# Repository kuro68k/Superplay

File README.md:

# SUPERPLAY

SUPERPLAY is an arcade joystick controller system. It consists of serveral parts.

The main SUPERPLAY PCB is fitted to the joystick and can either connect via USB or a custom KBUS. Both use the same USB cable. Configuration is via a Windows app called SPConfig.

SUPERPLAY supports up to 16 buttons, multiple autofire configurations with selectable fire rate, multiple options for switching modes and rotary joysticks (Seimitsu LS-30, used by SNK) for games like Midnight Resistance. Rotary joystick support is compatible with MAME, and configurable. SUPERPLAY also supports expansion boards via an expansion header, similar to Arduino sheilds.

####True zero lag

Many joystick controllers claim to be zero lag, but as FPS players know USB introduces some delay. USB HID devices are polled at 120Hz maximum, resulting in up to 8ms of lag (1/2 a frame at 60Hz). FPS players hack the Windows mouse driver to increase the poll rate, but it doesn't work for joysticks.

SUPERPLAY uses the excellent vJoy (vjoystick.sourceforge.net) and a custom USB interface to increase the polling rate to 1000Hz, reducing lag down to 1ms maximum. This gives true zero, arcade/console levels of input lag (i.e. none).

####Autofire

SUPERPLAY has a special autofire implementation that allows the player to set a precise frequency, and ensures that a button press is always registered when the button is first pushed. Simple autofire systems switch in a square wave, so the button press is sometimes not registered until the "on" part of the square wave comes around.

####KBUS

Aside from USB, SUPERPLAY can be connected to KBUS devices. Currently under development are a supergun with KBUS support, and a number of "recievers". Recievers connect to games consoles. The first is planned to support Playstation 1/2, Saturn and Dreamcast. Unfortunately due to licencing agreements Dreamcast support will not be published.

KBUS uses a simple 3.3V "RS232" compatible protocol, that can be easily implemented on low cost microcontrollers.

####Other stuff

A HID based USB bootloader will be provided for firmware and configuration updates. See my other projects for code.

The main SUPERPLAY PCB uses an XMEGA 128A3U microcontroller. This might be revised down to a 64KB in future. The project opens with Atmel Studio 6.2. Schematic and gerbers created in Eagle. V1.0 hardware has been built, V1.1 corrects a few issues.

SPConfig is built in Visual Studio 2013 Community Edition. I uses MahApps.Metro to create a "modern" UI.

Everything is licenced under GPL v3.

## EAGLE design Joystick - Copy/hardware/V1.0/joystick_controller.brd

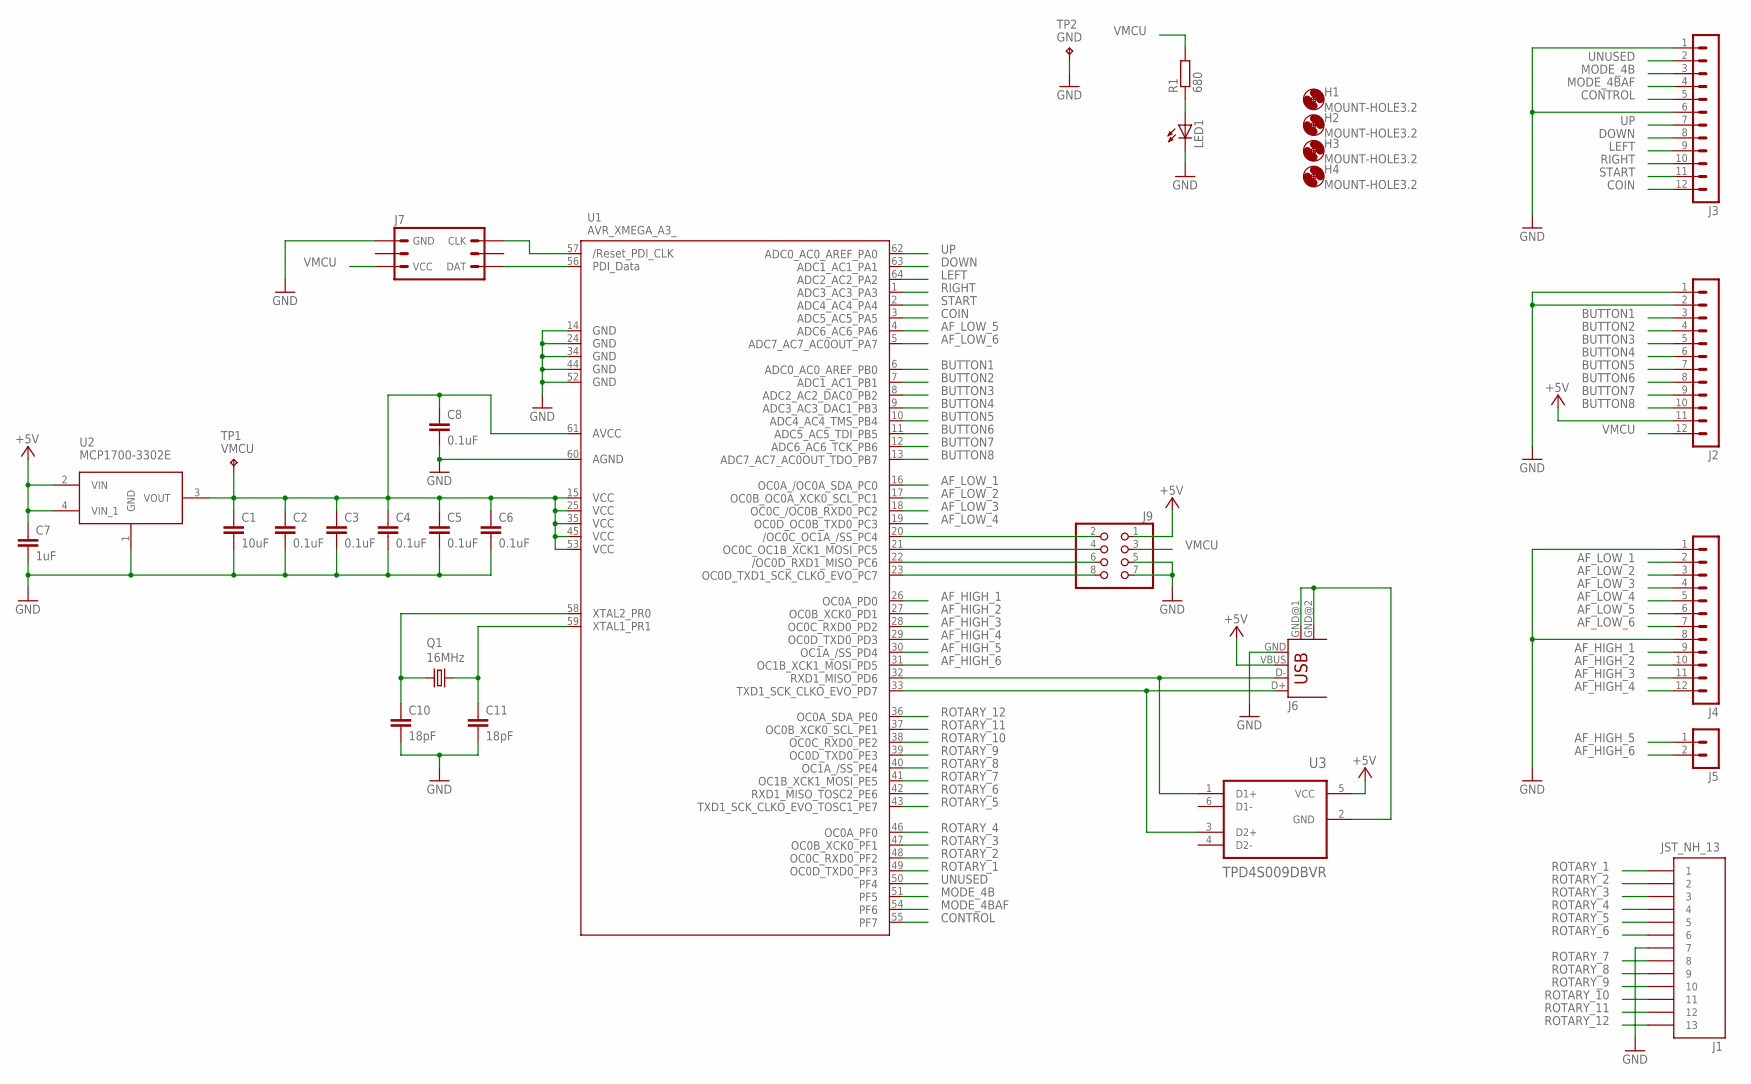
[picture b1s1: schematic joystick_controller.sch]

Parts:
C1: 10uF; C0805
C2, C3, C4, C5, C6, C8: 0.1uF; C0805
C7: 1uF; C0805
C10, C11: 18pF; C0805
H1, H2, H3, H4: MOUNT-HOLE3.2; 3,2
J1: JST_NH_13; JST_NH_13_RA
J2, J3, J4: CON-3.5TERM-12
J5: CON-3.5TERM-2
J6: USB-B-H
J7: PDI_HEADER; MA03-2
J9: PINHD-2X4; 2X04
LED1: LEDCHIP-LED0805; CHIP-LED0805
Q1: 16MHz; HC49/S
R1: 680; R0805
TP1: VMCU; HARWIN-S1751-46
TP2: GND; HARWIN-S1751-46
U1: AVR_XMEGA_A3_; TQFP64
U2: MCP1700-3302E; SOT150P400X160-4N
U3: TPD4S009DBVR; SOT95P280X145-6N

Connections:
+5V: C7.1, J2.11, J6.VBUS, J9.1, U2.2 (VIN), U2.4 (VIN_1), U3.5 (VCC)
AF_HIGH_1: J4.9, U1.26 (PD0)
AF_HIGH_2: J4.10, U1.27 (PD1)
AF_HIGH_3: J4.11, U1.28 (PD2)
AF_HIGH_4: J4.12, U1.29 (PD3)
AF_HIGH_5: J5.1, U1.30 (PD4)
AF_HIGH_6: J5.2, U1.31 (PD5)
AF_LOW_1: J4.2, U1.16 (PC0)
AF_LOW_2: J4.3, U1.17 (PC1)
AF_LOW_3: J4.4, U1.18 (PC2)
AF_LOW_4: J4.5, U1.19 (PC3)
AF_LOW_5: J4.6, U1.4 (PA6)
AF_LOW_6: J4.7, U1.5 (PA7)
BUTTON1: J2.3, U1.6 (PB0)
BUTTON2: J2.4, U1.7 (PB1)
BUTTON3: J2.5, U1.8 (PB2)
BUTTON4: J2.6, U1.9 (PB3)
BUTTON5: J2.7, U1.10 (PB4)
BUTTON6: J2.8, U1.11 (PB5)
BUTTON7: J2.9, U1.12 (PB6)
BUTTON8: J2.10, U1.13 (PB7)
COIN: J3.12, U1.3 (PA5)
CONTROL: J3.5, U1.55 (PF7)
DOWN: J3.8, U1.63 (PA1)
D_M: J6.D-, U1.32 (PD6), U3.1 (D1+)
D_P: J6.D+, U1.33 (PD7), U3.3 (D2+)
GND: C1.2, C2.2, C3.2, C4.2, C5.2, C6.2, C7.2, C8.2, C10.2, C11.2, J1.7, J2.1, J2.2, J3.1, J3.6, J4.1, J4.8, J6.GND, J7.6 (GND), J9.5, J9.7, LED1.C, TP2.P$1, U1.14 (GND1), U1.24 (GND2), U1.34 (GND3), U1.44 (GND4), U1.52 (GND5), U1.60 (AGND), U2.1 (GND)
LEFT: J3.9, U1.64 (PA2)
MODE_4B: J3.3, U1.51 (PF5)
MODE_4BAF: J3.4, U1.54 (PF6)
unnamed: LED1.A, R1.1
unnamed: J7.1 (DAT), U1.56 (PDI_DATA)
unnamed: J7.5 (CLK), U1.57 (RESET)
unnamed: J6.GND@1 (GND), J6.GND@2 (GND), U3.2 (GND)
unnamed: J9.8, U1.23 (PC7)
unnamed: J9.6, U1.22 (PC6)
unnamed: J9.4, U1.21 (PC5)
unnamed: J9.2, U1.20 (PC4)
unnamed: C11.1, Q1.2, U1.59 (PR1)
unnamed: C10.1, Q1.1, U1.58 (PR0)
RIGHT: J3.10, U1.1 (PA3)
ROTARY_1: J1.1, U1.49 (PF3)
ROTARY_2: J1.2, U1.48 (PF2)
ROTARY_3: J1.3, U1.47 (PF1)
ROTARY_4: J1.4, U1.46 (PF0)
ROTARY_5: J1.5, U1.43 (PE7)
ROTARY_6: J1.6, U1.42 (PE6)
ROTARY_7: J1.8, U1.41 (PE5)
ROTARY_8: J1.9, U1.40 (PE4)
ROTARY_9: J1.10, U1.39 (PE3)
ROTARY_10: J1.11, U1.38 (PE2)
ROTARY_11: J1.12, U1.37 (PE1)
ROTARY_12: J1.13, U1.36 (PE0)
START: J3.11, U1.2 (PA4)
UNUSED: J3.2, U1.50 (PF4)
UP: J3.7, U1.62 (PA0)
VMCU: C1.1, C2.1, C3.1, C4.1, C5.1, C6.1, C8.1, J2.12, J7.2 (VCC), J9.3, R1.2, TP1.P$1, U1.15 (VCC1), U1.25 (VCC2), U1.35 (VCC3), U1.45 (VCC4), U1.53 (VCC5), U1.61 (AVCC), U2.3 (VOUT)

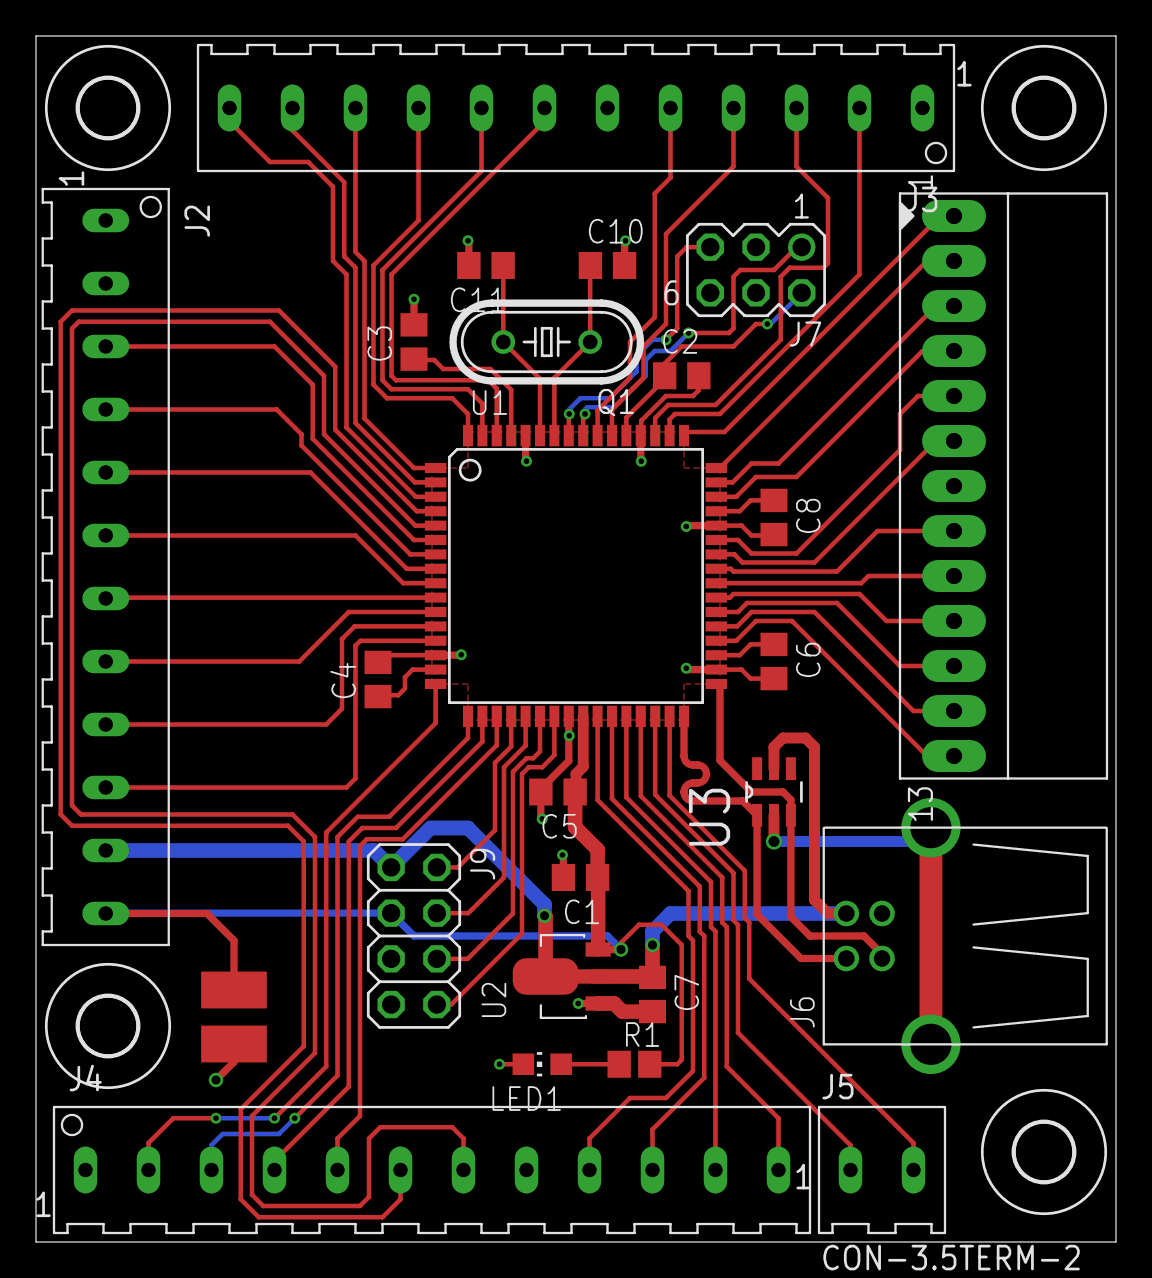
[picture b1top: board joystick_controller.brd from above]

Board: 2 copper layers, 60.0 x 67.0 mm, 30 parts (0 on the bottom side), 57 nets.

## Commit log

2015-08-23 :confetti_ball: Added .gitattributes
2015-08-23 Updated .gitignore
2015-08-23 Added licence
2015-08-25 Added autofire
2015-08-25 Autofire updates
    Added AF toggle mode
    Fixes for AF modes and settings
2015-08-26 Vendor custom interface enabled
    + Vendor interface
2015-08-27 SPFeeder added
    SPFeeder app for vJoy to enable true zero lag
2015-08-27 Vendor USB interface
2015-09-01 KBUS over USB
2015-09-01 KBUS support
2015-09-01 HID descriptor update
    Moved descriptor to separate file, removed POV control
2015-09-02 KBUS over USART
2015-10-13 More flexible config (wip)
    Config made less dependent on hardware
2015-10-14 Compiles (wip)
    Re-worked all config and reporting stuff to at least compile OK
2015-10-14 Generalized config checking
2015-10-14 Fixed physical -> logical mapping
2015-10-15 Enabled rotary inputs for HID again
2015-10-19 Added mapgen
    mapgen tokenizes text files into config data for SUPERPLAY
2015-10-20 Completely free mapping
2015-10-20 Updated mapgen to free mapping support
2015-10-23 Added bootloader
2015-10-26 Fixed EEPROM writing
2015-10-26 Fixed SP_CommonLPM breaking NVM controller
2015-10-27 Added HID support to mapgen
2015-11-01 Fixed default mapping
    Logical map == 0 means end of list
2015-11-01 Fixed and tested bootloader
    Also fixed EEPROM writing and fuses
2015-11-24 Added WCID support
2015-11-24 Updated GUID, clean up
2015-12-03 Reduced watchdog timeout to 128ms
2016-03-11 Feeder now builds
    Added vJoyInterface suff, feeder now builds and runs
2016-04-04 DMA RX for USART
2016-04-15 Fixed a couple of compiler warnings
2016-04-15 Started on AUX button output
2016-04-18 Aux buttons complete, to be tested
2016-05-04 Added Atari/Commodore Receiver
2016-05-16 PSX receiver for E5
2016-07-14 Protocol documentation for KBUS
2016-07-15 Clarified activation timing
2016-07-15 PCE and hardware r2 support
2016-07-18 Improved polling scheme
2016-11-11 Receiver E5 hardware added
2016-11-14 Finished adding footprints
2016-11-14 Removed backup file
2016-11-14 Added optional MISO pull-up
2016-11-14 Fixed a few minor schematic errors
2016-11-14 Changed PDI header to 2.54mm pitch TH
2016-11-14 Started work on PCB layout
2016-11-14 Set up design limits
2016-11-14 Routing try 1
2016-11-14 Routing try 2
2016-11-14 Added mounting holes
2016-11-15 50x30mm layout
2016-11-15 Rounded corners off
2016-11-15 Boost/linear reg
2016-11-15 2 layer power routing try 1
2016-11-15 Added missing series termination resistors for KBUS
2016-11-15 Finished signal routing
2016-11-15 2 layer power routing part 2
2016-11-15 4 layer all routed
    No unrouted nets
2016-11-15 Unconnected net fixed, DRC passes
2016-11-15 Added autosave files to ignore list
2016-11-16 Changed all holes to min 3mm, need to fix DRC errors
2016-11-16 Passed DRC again
2016-11-16 USB connector was on wrong side of the board
2016-11-16 Silk + mounting holes changed to M2.5
2016-11-16 Silkscreen tidied up
2016-11-16 Metadata + PDF schematic
2016-11-16 SVG output + settings
2016-11-17 Laser cut case design
2016-11-18 Added some extra fields for BOM generation with kibom
2016-11-18 Rounded case design
2016-11-22 Added BOM + notes
2016-11-25 Added Ponoko manufacturing files
2017-01-06 Started work on new ConfigGen
2017-01-06 Converted to AS7 project
2017-01-12 Generates binary blobs
2017-01-12 Custom binary field support
2017-01-13 Handles arrays
2017-01-13 Trying to fix array marshalling
2017-01-16 Handles variable length arrays in configs
2017-01-17 HEX file generation working
2017-01-17 Refactored HEX code into class
2017-01-19 Switched to Keio.Utils..dll for text utils and Intel Hex functions
2017-01-19 Removed random firmware dump
2017-01-20 Added CRC32 to config binary output
2017-01-20 Added af_remember_state
2017-01-20 Started adding new configuration format
2017-01-20 Added custom byte stream formatting for padding
2017-01-23 Removed padding
2017-01-23 New config system
2017-01-23 Builds with new config
2017-01-24 New autofire
2017-01-24 AF duty cycle settings
2017-01-24 Updated I/O mapping
2017-01-24 New output mapping
2017-01-25 Enabled output and AF
2017-01-25 Tidied up HID
2017-01-26 KBUS sends long reports
2017-01-26 Set minimum AF frequency
2017-01-26 Migrated to Atmel Studio 7.0
2017-01-26 Start bootloader on software reset instead of EEPROM flag
2017-01-27 eeprom_marker unused
2017-01-27 Best to keep reset flags for application
2017-01-27 Use watchdog to reset out of bootloader
2017-01-27 Corrected bootloader entry logic, added button
2017-01-27 Added optional LED
2017-01-27 Clean up
2017-01-27 Header fixes
2017-01-27 Unused forced mapping
2017-01-27 Config ID registry
2017-01-27 AC config
2017-01-27 Many to one mapping support
2017-01-27 New report format
2017-01-27 Reworking KBUS to not be a state machine
2017-01-29 Fixed flexible length array/sizeof() issue
2017-01-29 HID working, AF broken
2017-01-29 24MHz from PLL/2
2017-01-29 Fixed AF timer calculation
2017-01-29 Autofire fixed
2017-01-29 Better way to calculate struct size
2017-02-02 Replaced state machine
2017-02-02 Fixed input mapper
2017-02-02 New config / mapping
2017-02-03 Atari output enabled
2017-02-03 - redundant clear
2017-02-06 Widened board, added button
2017-02-06 Fixed position of USB
2017-02-07 Cover mapgen
2017-02-08 Version per host
2017-02-08 Top silk
2017-02-08 Bottom silkscreen
2017-02-12 Receiver 2.1 release
2017-02-12 New Playstation receiver
2017-02-12 Removed atari.S from PSX
2017-05-10 Changed programmer
2017-05-10 moved joystick bootloader directory
2017-05-10 moved receiver directories
2017-05-10 removed old mapgen
2017-05-10 Cleaned up receiver hardware directory
2017-05-10 Manufactured releases
2017-05-10 Composite -> HID only USB device
2017-05-10 Removed HID enable/disable feature
2017-05-10 Removed vendor specific protocol
2017-05-10 Formatting
2017-05-10 Fixed descriptor
2017-05-10 Boot to app
2017-05-11 Simplfied entry conditions
2017-05-11 Fixed button entry mechanism
2017-05-11 Enabled bootloader
2017-05-11 Port name typo
2017-05-11 Removed unwanted copy
2017-05-11 Moved expansion port to add I2C
2017-05-11 V2.0 updates
2017-05-11 V2.0 schematic
2017-05-12 Assigned footprints
2017-05-12 Finished foorprint assignments
2017-05-12 Fixed ERCs
2017-05-13 Ignore hex files
2017-05-14 Started PCB layout
2017-05-16 30x50mm board
2017-05-16 Routing attempt
2017-05-17 Rewired to make PCB layout easier
2017-05-17 Routing looks successful
2017-05-17 Routing power
2017-05-18 Routing finished, passes DRC
2017-05-18 Silkscreens
2017-05-18 Silkscreen
2017-05-19 Layer numbers
2017-05-20 Added SUPERPLAY logo
2017-05-20 Keio + graphic
2017-05-20 KEIO logo was backwards
2017-05-20 Gerbers
2017-05-26 Key functionality rework
2017-06-14 Added email
2017-06-16 Output
2017-06-16 V2.0 hardware changes
2017-06-19 V2 hardware and heavy optimization
2017-06-20 USART reports working
2017-06-20 USART mode detection
2017-06-21 Improved USB bus detection
2017-06-21 Old, removed
2017-06-21 Deprecated
2017-06-21 Test config file
2017-06-21 KeioUtils for CLI processing
2017-06-21 Meta keys with debounce
2017-06-21 Port mapping clean-up
2017-06-21 V1/V2 hardware support
2017-07-03 Ported changes from joystick to KBUS
2017-07-03 KBUS changes from joystick
2017-07-03 TX with CRC
2017-07-03 New connection handshake
2017-07-03 Expected response
2017-07-03 USART mode response
2017-07-04 Removed aux, added preamble to RX
2017-07-04 Preamble support
2017-07-04 Enable RX
2017-07-09 Min hole size fixed, drill file for Seeed OK
2017-07-10 Better naming
2017-07-10 32MHz CPU clock, KBUS command code
2017-07-11 Config loading over KBUS
2017-07-11 Fast memory copy/clear functions
2017-07-11 Faster button mapping
2017-07-11 Fixed input mapping
2017-07-11 kbus_matrix now part of input_matrix
2017-07-12 Schematic PDF and BOM refresh
2017-07-12 Added BOM
2017-07-12 Layout overviews
2017-07-12 Updated BOM
2017-09-19 Migrated to 64A3U
2017-09-19 Not needed
2017-09-19 Upgraded to Kicad 4.0.7
2017-10-01 Inverted I/O for more efficient mapping
2017-10-08 Upgraded
2017-10-08 Disabled debug output
2017-10-08 Cleaned up builds
2017-10-08 Bootloader entry
2017-11-04 Testing on hardware V2
2018-04-01 Debugging
2018-04-08 Replaced ASF with new USB stack
2018-06-04 New stack working
2018-06-04 sp_driver duplicated in xmega.h/.S
2018-06-04 unused header
2018-06-04 WCID working
2018-06-04 Removed debug code
2018-08-22 DFU bootloader
2018-08-22 Fixed DFU runtime
2018-08-23 Binary bootloaders
2018-09-02 Button 1 entry condition

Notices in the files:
Joystick - Copy/hardware/V1.0/joystick_controller.brd:
(C)2015 Paul Qureshi
